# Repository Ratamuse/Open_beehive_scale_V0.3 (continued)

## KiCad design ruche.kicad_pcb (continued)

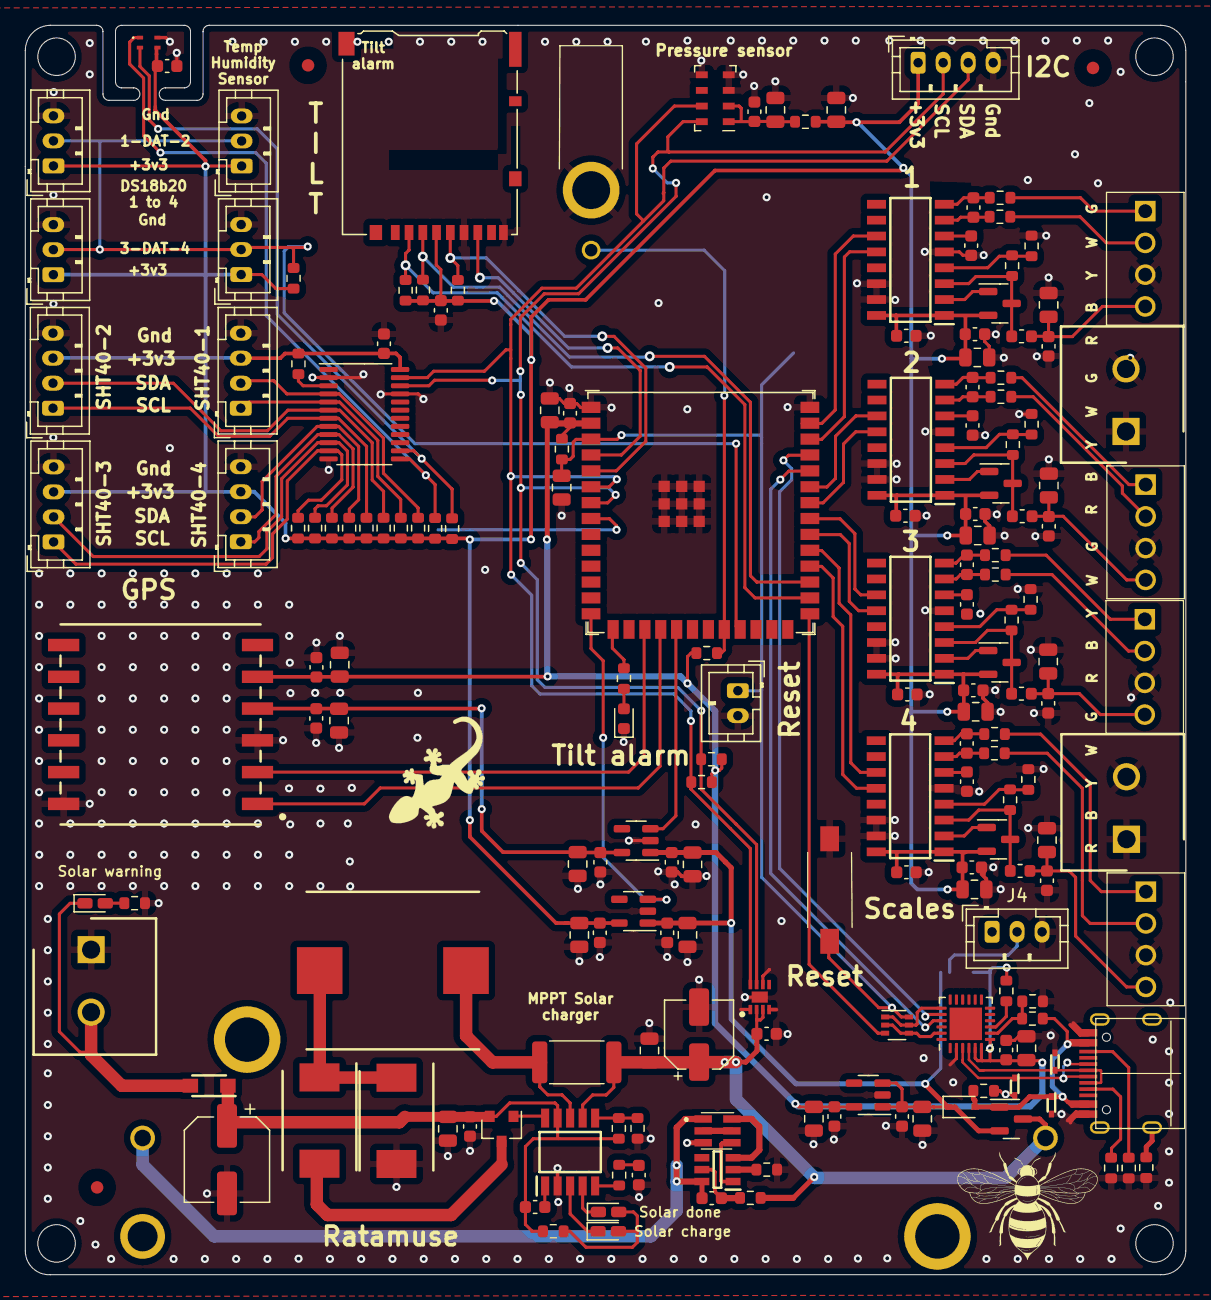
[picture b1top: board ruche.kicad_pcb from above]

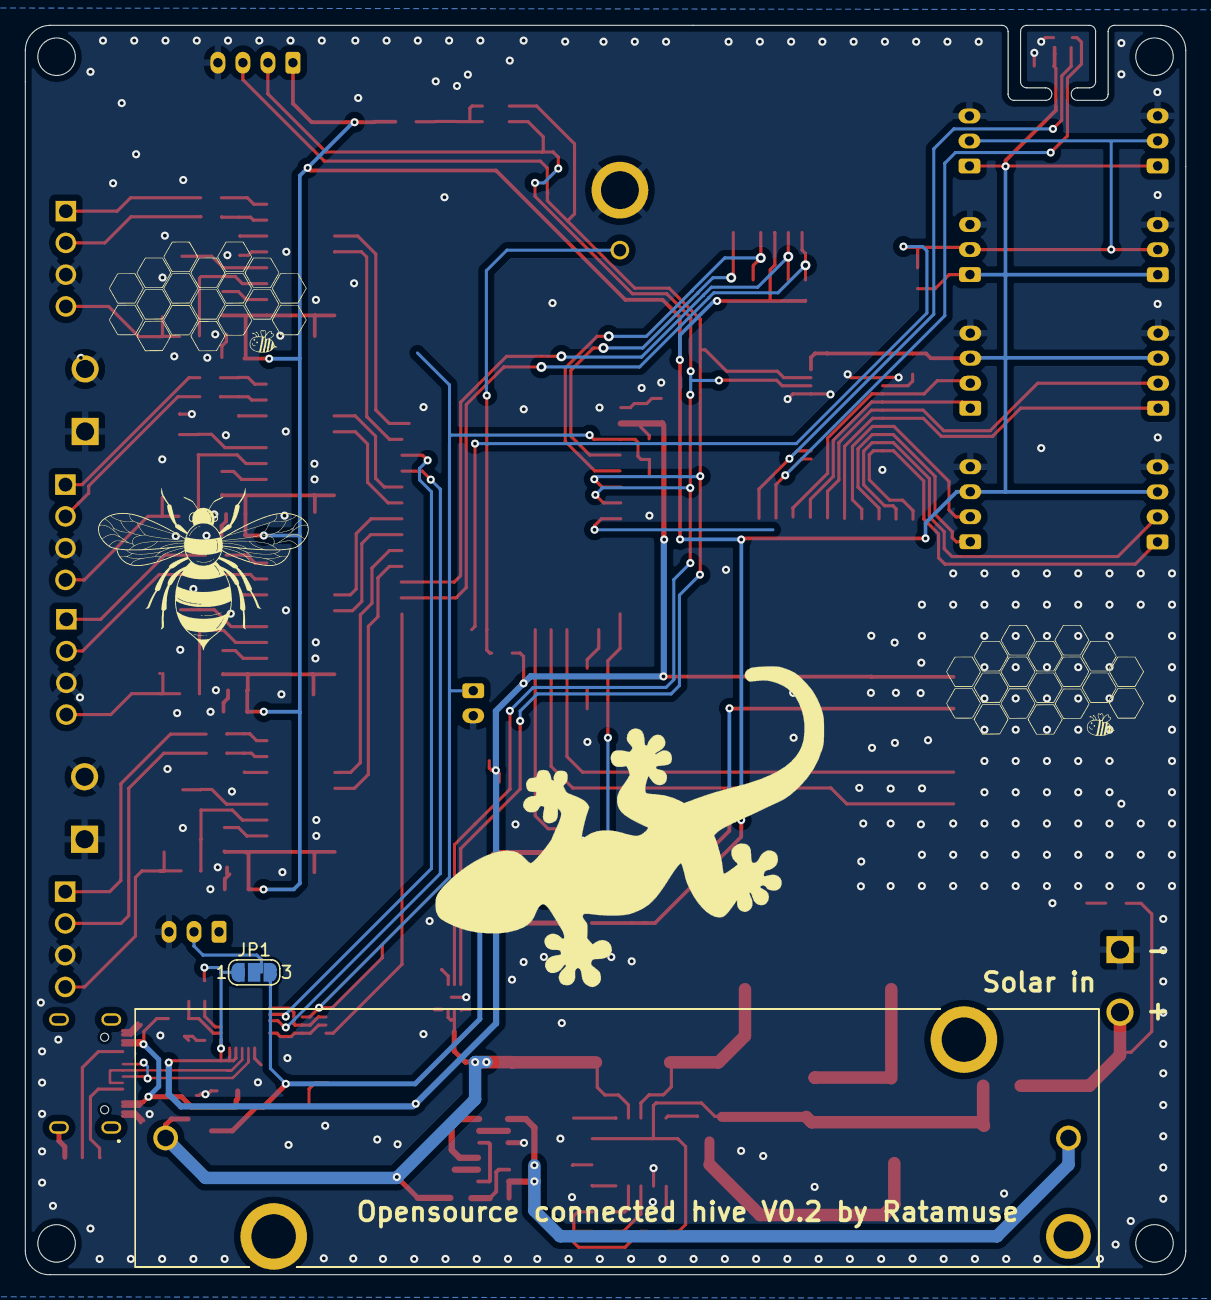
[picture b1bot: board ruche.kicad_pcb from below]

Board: 2 copper layers, 92.8 x 99.9 mm, 184 parts (2 on the bottom side), 111 nets.

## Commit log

2022-11-20 Mise à jour
